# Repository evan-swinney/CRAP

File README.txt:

The Common Rocketry Avionics Package (CRAP) project is a rocket avionics package, designed specifically for UAH Space Hardware Club to be flown on the multistage team's rocket.  This payload will also serve as an in-house alternative to L1 Certifications and general rocketry for data collection and GPS tracking.  This payload will fire all rocket ordance and motors as well as provide data telemetry and storage.

. . . . . . . . . . . . . . . . . . . . . . . . . . . . . . . . . . . . . . . . . . . 

Designed by:
Cooper Barry - Team lead
Evan Swinney - Hardware design
James Biaglow - Hardware design and integration
Daniel Corey - Software Design
Will Watson - Software Design

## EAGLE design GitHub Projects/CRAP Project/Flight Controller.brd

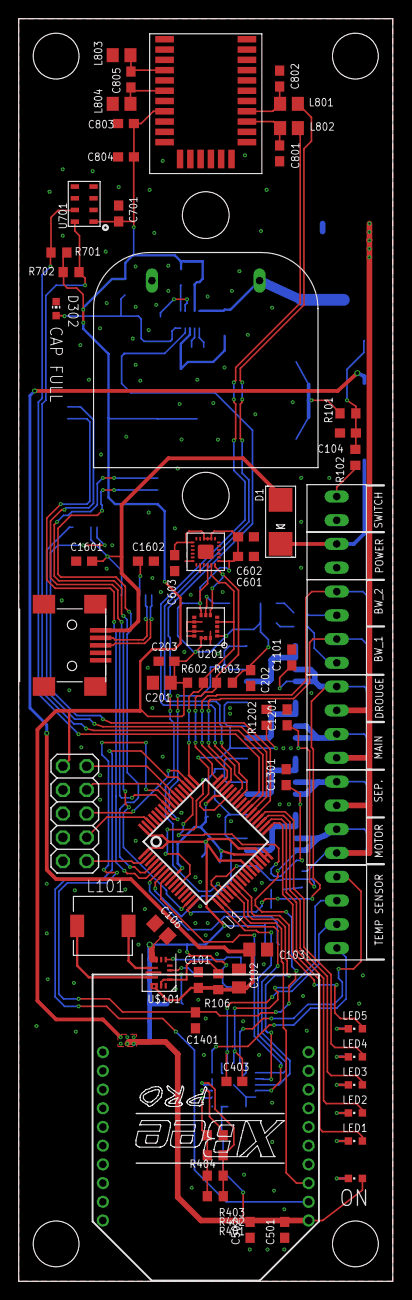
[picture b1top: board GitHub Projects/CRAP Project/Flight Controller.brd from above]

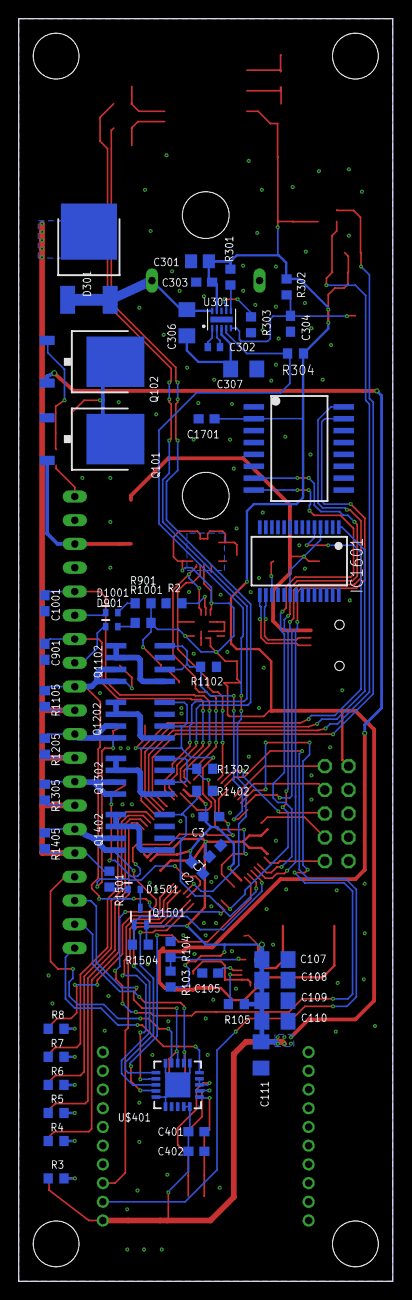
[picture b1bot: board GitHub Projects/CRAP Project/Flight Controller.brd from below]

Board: 2 copper layers, 40.0 x 135.0 mm, 127 parts (60 on the bottom side), 94 nets.

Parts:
C1: 4.7u; C0603
C2, C303, C502: 1u; C0603
C3, C105, C701: 100n; C0603
C101: 10u; C0603
C102, C103, C106, C201: 10u; C0805
C104: 2.2 u; C0603
C107, C108, C109, C110, C111: 22u; C1206
C202, C203, C304, C501, C601, C603, C901, C1001, C1101, C1201, C1301, C1401, C1601, C1602, C1701: 0.1u; C0603
C301: 2.2u; C0805
C302: 1u; C0402
C305: AVX_1F_5V_FOLDED
C306, C307: 100u; C1206
C401, C402: 0.1 u; C0603
C403: 100 n; C0603
C602: 10n; C0603
C801, C802, C803: 22p; C0603
C804: 2.2u; C0603
C805: 18p; C0603
CN1: USB-MINIB
D1: B160-13-F; SMADIODE
D301: RB095BM-30; TO252
D302: LTST-C193KRKT-2A; CHIP-LED0603
D901, D1001, D1501: CES521SOD523; SOD523
IC1601: FT232RL; SSOP28
J1, J101: 2POS_SCREWTERM; 2POS_0.1
J2, J3, J4, J5: 4POS_SCREWTERM; 4POS_0.1
JP1: 2X05
L101: B82462G4102M; B82462G4
L801, L802: 47n; R0805
L803, L804: 2.2u; R0805
LED1, LED2, LED3, LED4, LED5: BLUE; CHIPLED_0603
ON: RED; CHIPLED_0603
Q101, Q102: IPD042P03L3G; TO252
Q1102, Q1202, Q1302, Q1402: DMG4800LSD; SO-08
Q1501: PMF170XP; SOT323
R2, R106, R301, R304, R901, R1001: 10k; R0603
R3, R4, R5, R6, R7, R8: R0603
R101, R105: 100k; R0603
R102: 1k; R0603
R103: 470k; R0603
R104: 150k; R0603
R302, R701, R702: 2.2k; R0603
R303: 12k; R0603
R401, R402, R403: 1.2 k; R0603
R404: 10 M; R0603
R602, R603: 2.2K; R0603
R1102, R1202, R1302, R1402, R1501, R1504: 10 k; R0603
R1105, R1205, R1305, R1405: 1M; R0603
U1: G55J19; SQFP-S-10X10-64
U201: HDLIS100DL; TFLGA16L
U301: LTC3225; DFN10-2X3
U601: MPU9250; QFN-24
U701: MS5611
U1701: MT29F1G01; SOP16
U$101: TPS6307X; VQFN15_2.5X3
U$401: MAX31865; TQFN20-5X5
U$801: M10478-A3
XB501: XBEE-PRO

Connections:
+3V3: C1.1, C106.1, C107.1, C108.1, C109.1, C110.1, C111.1, C201.1, C202.1, C203.1, C301.1, C303.1, C401.1, C402.1, C501.1, C502.1, C601.1, C602.1, C603.1, C701.1, C803.2, C804.2, C1701.1, JP1.1, ON.A, Q1501.3, R103.2, R105.2, R301.2, R302.2, R304.2, R602.2, R603.2, R701.2, R702.2, R901.2, R1001.2, R1504.2, U1.1, U1.27, U1.31, U1.32, U1.64, U201.P1, U201.P8, U201.P14, U201.P15, U301.P9, U601.1, U601.8, U601.9, U601.10, U601.13, U601.22, U701.1, U701.2, U1701.2, U$101.P7, U$101.P8, U$401.19, U$401.20, U$801.8, XB501.1
+5V: C1601.2, CN1.VBUS, D1.A, IC1601.4, IC1601.20
BREAKWIRE1:N$1: D901.A, R901.1
BREAKWIRE2:N$1: D1001.A, R1001.1
BW1_STATUS: C901.1, J5.2, U1.46
BW2_STATUS: C1001.1, J5.4, U1.47
C4:N$2: D1501.A, Q1501.1
C4:N$3: D1501.C, R1501.2
DCDC_REGULATOR:N$1: Q101.3, Q102.3, R101.2
DCDC_REGULATOR:N$3: L101.P$1, U$101.P11
DCDC_REGULATOR:N$4: C104.1, Q102.1, R101.1, R102.1
DCDC_REGULATOR:N$5: L101.P$2, U$101.P9
DCDC_REGULATOR:N$6: J101.2, R102.2
DCDC_REGULATOR:N$7: C105.1, U$101.P3
DCDC_REGULATOR:N$9: R105.1, U$101.P2
DCDC_REGULATOR:N$10: R103.1, R104.2, U$101.P5
DCDC_REGULATOR:N$11: R106.1, U$101.P1, U$101.P14
DCDC_REGULATOR:VIN: C101.1, C102.1, C103.1, Q102.2, R106.2, U$101.P12, U$101.P13
FC1-: C1401.1, J3.2, Q1402.7, Q1402.8, R1405.1, U1.56
FC1_FIRE: Q1402.2, Q1402.4, R1402.2, U1.7
FC2-: C1301.1, J3.4, Q1302.7, Q1302.8, R1305.1, U1.52
FC2_FIRE: Q1302.2, Q1302.4, R1302.2, U1.11
FC3-: C1201.1, J4.2, Q1202.7, Q1202.8, R1205.1, U1.19
FC3_FIRE: Q1202.2, Q1202.4, R1202.2, U1.44
FC4-: C1101.1, J4.4, Q1102.7, Q1102.8, R1105.1, U1.16
FC4_FIRE: Q1102.2, Q1102.4, R1102.2, U1.58
FC_!CONT_EN: Q1501.2, R1504.1, U1.6
FIRING_CIRCUIT1:N$1: Q1402.1, Q1402.5, Q1402.6
FIRING_CIRCUIT2:N$1: Q1302.1, Q1302.5, Q1302.6
FIRING_CIRCUIT3:N$1: Q1202.1, Q1202.5, Q1202.6
FIRING_CIRCUIT4:N$1: Q1102.1, Q1102.5, Q1102.6
FT1:N$5: C1602.1, IC1601.17
GND: C1.2, C2.1, C3.1, C101.2, C102.2, C103.2, C104.2, C105.2, C106.2, C107.2, C108.2, C109.2, C110.2, C111.2, C201.2, C202.2, C203.2, C301.2, C303.2, C304.2, C305.2, C307.2, C401.2, C402.2, C501.2, C502.2, C601.2, C602.2, C603.2, C701.2, C801.2, C802.2, C803.1, C804.1, C901.2, C1001.2, C1101.2, C1201.2, C1301.2, C1401.2, C1601.1, C1602.2, C1701.2, CN1.GND, D302.C, IC1601.7, IC1601.18, IC1601.21, IC1601.25, J1.2, J101.1, JP1.3, JP1.5, JP1.9, L803.1, L804.1, Q101.1, Q1102.3, Q1202.3, Q1302.3, Q1402.3, R2.1, R3.1, R4.1, R5.1, R6.1, R7.1, R8.1, R104.1, R303.1, R1102.1, R1202.1, R1302.1, R1402.1, U1.13, U1.29, U1.53, U201.P5, U201.P10, U201.P12, U201.P13, U201.P16, U301.P8, U301.P11, U601.18, U601.20, U701.3, U701.4, U701.5, U1701.10, U$101.P4, U$101.P6, U$101.P10, U$101.P15, U$401.6, U$401.10, U$401.15, U$401.16, U$401.EXP, U$801.1, U$801.2, U$801.3, U$801.5, U$801.7, U$801.9, U$801.15, U$801.16, U$801.17, U$801.19, U$801.22, U$801.23, U$801.24, U$801.25, U$801.27, U$801.28, XB501.10
GPS1:N$1: C805.1, L803.2, U$801.4
GPS1:N$2: C802.1, L801.1, U$801.21
GPS1:N$3: C801.1, L802.1, U$801.20
GPS1:N$4: C805.2, L804.2, U$801.6
GPS_RX: L801.2, U1.42
GPS_TX: L802.2, U1.43
IMU_SCL: R602.1, U1.49, U201.P4, U601.23
IMU_SDA: R603.1, U1.48, U201.P6, U601.24
MEM_!CS: U1.15, U1701.7
MEM_MISO: U1.4, U1701.8
MEM_MOSI: U1.5, U1701.15
MEM_SCK: U1.57, U1701.16
MS5611_SCL: R702.1, U1.39, U701.8
MS5611_SDA: R701.1, U1.40, U701.7
unnamed: JP1.2, U1.54
unnamed: JP1.4, U1.55
unnamed: JP1.6, U1.50
unnamed: JP1.8, U1.62
unnamed: JP1.10, U1.2
unnamed: J2.1, U$401.5
unnamed: C403.1, J2.2, U$401.7
unnamed: C403.2, J2.3, U$401.8
unnamed: J2.4, U$401.9
unnamed: D1001.C, J5.3
unnamed: D901.C, J5.1
unnamed: R2.2, U201.P7
unnamed: LED1.C, R4.2
unnamed: LED2.C, R5.2
unnamed: LED3.C, R6.2
unnamed: LED4.C, R7.2
unnamed: LED5.C, R8.2
unnamed: ON.C, R3.2
ORD+: D301.3, J3.1, J3.3, J4.1, J4.3, R1105.2, R1205.2, R1305.2, R1405.2, R1501.1
ORDNANCE_POWER:N$1: C302.1, U301.P1
ORDNANCE_POWER:N$2: C302.2, U301.P2
ORDNANCE_POWER:N$3: C305.1, C306.1, D301.1, D301.2, U301.P10
ORDNANCE_POWER:N$4: C304.1, D302.A, R302.1, U301.P5
ORDNANCE_POWER:N$5: R301.1, U301.P6
ORDNANCE_POWER:N$6: R303.2, U301.P7
ORDNANCE_POWER:N$7: C306.2, C307.1, U301.P3
ORD_!SHDN: R304.1, U1.20, U301.P4
RTD:N$1: R401.2, R402.2, R403.2, R404.2, U$401.1
RTD:N$4: R401.1, R402.1, R403.1, U$401.3, U$401.4
RTD:N$5: R404.1, U$401.2
RTD_!CS: U1.18, U$401.13
RTD_MISO: U1.8, U$401.14
RTD_MOSI: U1.17, U$401.11
RTD_SCK: U1.22, U$401.12
UC_LED1: LED1.A, U1.33
UC_LED2: LED2.A, U1.34
UC_LED3: LED3.A, U1.35
UC_LED4: LED4.A, U1.36
UC_LED5: LED5.A, U1.23
USB_N: CN1.D-, IC1601.16
USB_P: CN1.D+, IC1601.15
USB_RX: IC1601.5, U1.37
USB_TX: IC1601.1, U1.38
VCC_IN: D1.C, J1.1, Q101.2
VDDOUT: C2.2, C3.2, U1.9, U1.30, U1.45
XBEE_RX: U1.21, XB501.3
XBEE_TX: U1.51, XB501.2

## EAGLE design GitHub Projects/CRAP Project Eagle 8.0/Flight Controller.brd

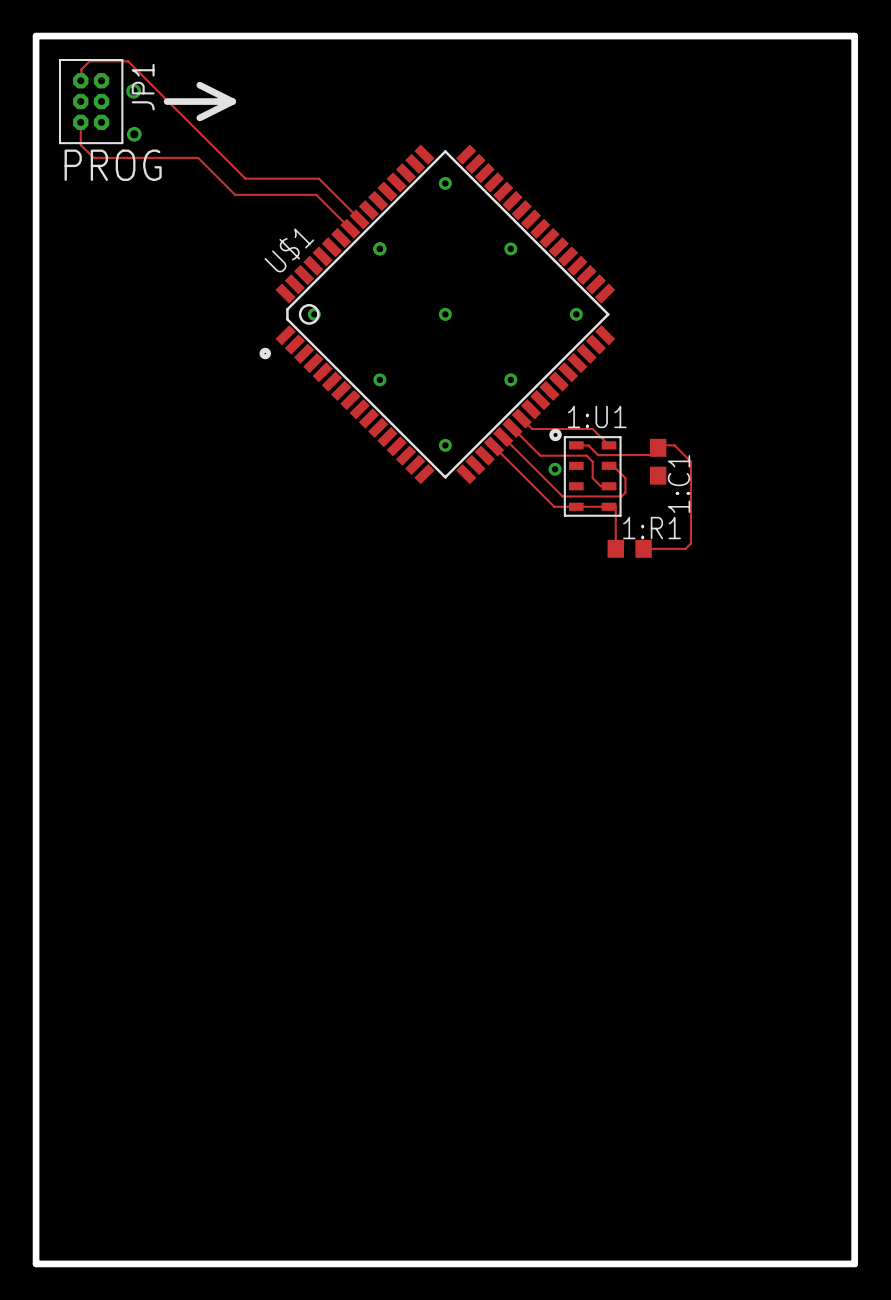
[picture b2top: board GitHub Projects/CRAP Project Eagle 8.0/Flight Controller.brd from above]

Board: 2 copper layers, 50.0 x 75.0 mm, 5 parts (0 on the bottom side), 8 nets.

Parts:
1:C1: 100n; C0603
1:R1: 10k; R0603
1:U1: MS5611
JP1: 2X03
U$1: XMEGA64A3U; TQFP64

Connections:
+3V3: 1:C1.1, 1:R1.2, 1:U1.1, JP1.5, U$1.15, U$1.25, U$1.35, U$1.45, U$1.53, U$1.61
GND: 1:C1.2, 1:U1.2, 1:U1.3, JP1.1, U$1.14, U$1.24, U$1.34, U$1.44, U$1.52, U$1.60
MS5611_CS: 1:R1.1, 1:U1.4, 1:U1.5, U$1.20
MS5611_MISO: 1:U1.6, U$1.22
MS5611_MOSI: 1:U1.7, U$1.21
MS5611_SCLK: 1:U1.8, U$1.23
X_PDI_DATA: JP1.6, U$1.56
X_RESET_PDI_CLK: JP1.2, U$1.57

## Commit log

2016-11-07 CRAP Project Readme file added
    Added a readme file.
2016-11-07 Copied SHC PCB Library to GitHub
    Added all of the nesscary files for DesignSpark Library
2016-11-07 Test
    Does this go to master or software?
2016-11-07 Fixing things
2016-11-07 Added PCB Library Files to PCB branch
2016-11-20 something
2016-11-20 Added personal Eagle library
2016-11-20 Added the CRAP Project's Board and Schematic Files
2016-11-20 Renamed folder
2017-01-21 New update
2017-01-21 Added LTC3225
    Made the schematic and the footprint for the LTC3225.
2017-01-22 Added MS library, created schematic for the MS5611 and xMega64A3U, and routed traces for the pressure sensor and PDI interface
    Things left to do:
    1. Create MPU9250
    2. Route MPU9250
    3. Create all parts for the power system
    4. Route all parts of the power system
    5. Create all parts for the ordance system
2017-01-23 Fixing my fuckups
    AKA removing the branches
2017-01-23 New readme file
2017-01-28 Minor changes with MS5611 and modules.
2017-01-28 Added Gitignore stuff
2017-01-29 Added V8.0 folder and MPU9250 part and lib
    Added the MPU block diagram to the schematic list. Also defined an
    Invensense library, which houses the MPU9250 along with a QFN-24 3x3x1mm
    package.
2017-02-05 Added TPS63070
    Added DCDC-Converter module on Flight Computer, and the TPS6307x device
    under the Texas library
2017-02-08 Updated power supply
    Worked some on the power supply module.
2017-02-09 Started ordnance module. Minor changes to power module
    Nothing new to power module—just modified the aesthetics. Added he
    ordnance module but mainly just the LTC3225 super-cap charging chip.
2017-02-10 Created sandbox.sch
    I am using the sandbox schematic to make figures for reports. It is not
    part of the final PCB.
2017-02-11 Added RTD module
    Started the RTD module on Flight Computer schematic
2017-02-23 Minor Changes
2017-02-23 Changed the .git ignore file to include more
    Added a lot of the file extensions that Eagle makes for 5min backups
2017-02-23 Updated .gitignore again
2017-02-23 Cleaned up a lot of the temp backup files
2017-02-23 Changed Module Offsets
    Changed module offsets to different values so that the giant names would
    go away. I feel that in future versions this feature will be more
    refined, since in V7.7 was the very first version it appeared in. The
    manual inside of the Eagle install in C:/ thankfully is updated with the
    new features and explains some of the new ways to do things better than
    anywhere I can find online. Seems that nobody online has these issues,
2017-02-24 Added Screw Terminals and Schematic Frames
    Added screw in terminals of the 2, 4, and 8 widths. They are at a
    2.54mm pitch (0.1').
    Also added in schematic frames to make our things look much fancier.
2017-02-25 RTD module nearly done
    1. RTD module is nearly done. Just need to figure out the connections in
    and out of modules, especially for the serial data lines and power.
    2. Touched up power and ordnance modules to include the correct ground
    symbols.
    Note: All this was done with the Eagle 7.x version files
2017-02-26 Started ordnance board
2017-02-26 Removed the other files that aren't needed anymore
    Didn't need those files since we can do all the work in the Flight
    Controller sheet with the submodules and whatnot.
2017-02-26 Added SAMG55 and AVR and SAM JTAG headers
    Created AVR JTAG headers for possible future use and also created SAM
    JTAG headers for immediate use.
    Added G55 into the root sheet and added recommended decoupling
    capacitors to VDDIO, VDDOUT, and VDDCORE.
2017-02-26 Fixed the board consistency by making a new board
    Do not modify the schematic unless the schematic and board are
    consistant. The easiest way to do this is to just have the board open
    when you open the schematic. This is why it asks if you want to open
    both when you first open the program.
    Also added a fancy logo to the Atmel chip's footprint, also found an
    existing part for the Xbee900 Pro, so I added that into the schematic
2017-02-26 Updated README.txt
2017-02-27 Module updates
    1. Fixed or added ports to the following modules: DC-DC Converter, RTD,
    Ordnance, and Firing Chains
    2. Fixed power pins within those modules
    3. Minor updates to the DC-DC Converter regarding the connections to the
    TPS63070
    4. Moved the RTD's screw terminal block to the top level sheet
2017-02-28 Modules, aesthetics, library fixes
    1. Renamed Ordnance to Ordnance Power. Moved Firing chains from inside
    this module to the top level schematic.
    2. Added Breakwire module with pins. Nothing done inside the module
    3. Added IMU module with pins. Nothing done inside the module
    4. Increased soldermask expansion on TPS63070 per datasheet inside the
    Texas.lbr
2017-02-28 Fixed library again
    Fixed CRAP Parts library again by adding reference designator to
    silkscreen
2017-02-28 Added frames and MPU-9250 into IMU module
    Also remade the board again because it broke.
2017-02-28 Added Micron 1Gbit memory module
    1. Changed all the text to the info layer
    2. Added the Micron 1Gbit memory module
    3. Routed power and ground to it
2017-03-01 Added super cap part, did prelim board layout
    1. Made a super capacitor part with a upright and folded variant.
    2. Talked with Davis about the dimensions of the board and came to the
    conclusion that 100mm tall will be alright. Also speculated that 100mm
    tall board would work with most club rockets, and confirmed with both
    supersonic teams that 100mm tall would be able to fit.
    3. Changed some of the modules in the upper level sheet to fit back on
2017-03-01 Changed silkscreen
    1. Changed the silkscreen from numbers with + and - to what they were
    going to be without + and -, because polarization doesn't matter when
    dealing with a resistive component.
    2. Also added the silkscreen names for the switch, temperature sensor,
    and power input.
2017-03-04 IMU, Breakwire, Firing Chain module updates
    1. Added CES521 diode to diode.lbr
    2. Added CES521 to breakwire and pyro firing chain modules
    3. Basic wiring of IMU module
    Issues needing to be resolved with Evan
    1. Address of IMU. There is a dangling resistor ready for this on the
    top level schematic.
2017-03-07 Added H3LIS100DL
    Added the H3LIS100DL to the ST-microelectronics library along with a
    3x3mm TFLGA-16 package. This device is in the HIGH_G module under
    Sensors. Things for Evan to consider on this push:
    1. Frame needed for the HIGH_G module schematic
    2. Data communication for H3LIS100DL: SPI or I2C?
    2a. If I2C, which address? Currently a resistor on the top level
2017-03-08 Ordnance power updates
    1. Fixed PGOOD LED on Ordnance Power module
    2. Wired output capacitors on Ordnance Power. This is a single super-cap
    configuration where two 100uF caps in series are needed fro the
    balancing circuitry.
    3. Added a frame to the HIGH_G module
    Another issue discovered:
2017-03-09 Updated .gitignore; added the .epf file to it
2017-04-01 Ordnance & Breakwire modules fixes
    1. In the Ordnance module: combined the PYRO+ and PWR to the same pin
    and called PWR/PYRO+. This is the ordnance power from the super caps.
    2. In the Ordnance module: combined CONT_STAT and PYRO– to the same pin
    and called CONT_STAT/PYRO–. Outside the modules on the top level
    schematic, I added long wires from this pin going to the left of each
    module. This is also the digital line for sensing continuity status of
2017-04-02 Set theme jekyll-theme-time-machine
2017-04-07 Major changes
    1. Cleaned up master level sheet
    2. Changed MS5611 from SPI to I2C
    3. Routed a lot
    4. Changed MPU9250 power structure on top level (was broken)
    5. Added serial communication lines to microcontroller
2017-04-07 Routed more, added GPS
    1. Added Antenova library
    2. Added our GPS to the Antenova library
    3. Placed GPS, which caused our power system to move, also increased
    board height by 5mm due to expected space constraints
    4. Moved our power system close to the Xbee
    5. Placed a MOSFET for the separation circuit
2017-04-11 Added EPF file to .gitignore, again....
2017-04-11 Routing, schematic changes
    1. Changed some schematic errors on the firing chains
    2. Routed more GPS, changed inductor on power supply, routed Xbee
2017-04-11 More routing changes
    1. Changed the power circuit 180 degrees to better fit the inductor
    2. Routed a lot of the ordance circuits and placed all MOSFETS
    3. Routed lots of power
    4. Oh god it's so crowded
2017-04-12 More routing
    1. Routed parts of the ordance
    2. Routed parts of the RTD
    3. Routed Parts of the breakwire
    4. Swapped RTD and breakwire headers to allow for actual routing because
    it was too cramped to fit the RTD's sensor chip in the area that the
    header was in
2017-06-19 Routed some of the RTD sensor
    Moved the RTD chip under the Xbee to have more room for capacitors and
    resistors later on
2017-06-27 Created Bourns.lbr and Diodes-Incorporated.lbr
2017-06-27 Minor Changes to some routing
    Having problems with using the alternate grid. Routing engine will not
    allow me to route on the alternate grid, which has stopped progress for
    the time being.
2017-07-20 Major revisions
    1. Made board 30mm taller to allow for more space in cramped enviroment.
    Deemed absolutely critical.
    2. Majorly changed the power turn-on and turn-off MOSFETs design and
    location to clear up room in the mid-board area
    3. Moved the super capacitor nearer to the top of the extended section,
    and also made it have a verticle orientation; should allow for better
2017-07-21 Routing of high-g IMU, regular IMU, firing circuits
    1. Chose communication lines for all sensors and memory to the uC
    2. Routed 100% the MPU9250
    3. Routed 100% the high-g accelerometer
    4. Routed 100% the breakwire circuits
    5. Routed 75% of the firing circuits
2017-07-22 More routing and schematic changes
    1. Finished 100% the schematic of all misc. connections that were going
    to things, such as all comms, all LED indication pins, and all
    enable/disable pins
    2. Added FTDI FT232R for serial to USB connectivity
    3. Routed the power line for the firing circuit from supercap
    4. Routed LED indication
2017-07-31 Major routing done
    1. Routed a bunch of stuff, so much stuff that I don't know what to put
    here.
    2. Added USB Mini connector and diode routed power to protect FTDI chip
    3. Added FTDI chip for USB to UART so we can dump data to USB
    4. Added holes forward and rear of the super cap so that we can screw
    things in to hold the super cap in place
2017-07-31 Routed GPS UART 100%
    1. Routed the GPS UART lines to the GPS and from the microcontroller.
2017-08-01 Finished placement of all parts
    1. Finished placing some misc items for the power converter, it is now
    100% complete
    2. Only thing left to do now is route some comms lines and some other
    misc lines and the board will be 100% complete.
2017-08-09 Finished routing CRAP [MAJOR]
    1. Finished routing everything but some ground plane issues
    2. Moved MS5611 to another location on the board because of space
    constraints that was making the groudplane too segmented to work
    properly.
    3. Finished routing the RTD 100%
